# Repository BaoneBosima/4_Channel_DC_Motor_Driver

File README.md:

# Quad-Channel Motor Driver Node (STM32 & CAN)

---

## 🚀 Key Features

- **Quad-Channel Drive:** Independent control of 4 DC motors using dual high-efficiency MOSFET H-Bridges.
- **Networked Intelligence:** Onboard STM32 microcontroller offloads low-level hardware timing from the main robot computer.
- **Industrial Communication:** CAN Bus (ISO 11898) interface with impedance-controlled differential routing for high noise immunity.
- **High-Efficiency Power Stage:** Integrated synchronous buck converter delivering 95% efficiency, drastically reducing thermal waste.
- **Robust Protection:** Hardware-level reverse polarity protection (P-MOSFET) and LC noise filtering.

---

## 🛠 Hardware Specifications

| | |
| --- | --- |
| **Microcontroller** | STM32F103C8T6 (ARM Cortex-M3, 72MHz) |
| **Motor Drivers** | 2x Toshiba TB6612FNG (1.2A Continuous / 3.2A Peak per channel) |
| **Power Regulation** | MP2315 Synchronous Buck Converter (12V to 3.3V @ 3A) |
| **Transceiver** | SN65HVD230 CAN Transceiver |
| **Input Voltage** | 12V DC Nominal |
| **Max Current Rating** | 4A Continuous (Board Total) |

---

## 📐 PCB Layout & Stackup

The board was designed in KiCad 8.0 utilizing a 4-layer, impedance-controlled stackup to ensure signal integrity in a mixed-signal environment.

| Layer | Description |
| --- | --- |
| **Layer 1 (Top - Signal)** | Component placement, high-speed MCU routing, and localized thermal ground pours. |
| **Layer 2 (Inner - GND Plane)** | Solid, unbroken reference plane to minimize loop inductance, suppress EMI, and prevent ground bounce. |
| **Layer 3 (Inner - Power Plane)** | Dedicated 12V distribution plane, calculated via IPC-2221 standards to handle high-current motor transients with minimal IR drop. |
| **Layer 4 (Bottom - Signal)** | Cross-under routing, jumper traces, and bottom thermal reliefs. |

### Thermal Management

Extensive via stitching is implemented around the H-Bridge drivers and the buck converter. This couples the surface copper to the internal planes, effectively turning the PCB itself into a heatsink to handle stall currents without external cooling hardware.

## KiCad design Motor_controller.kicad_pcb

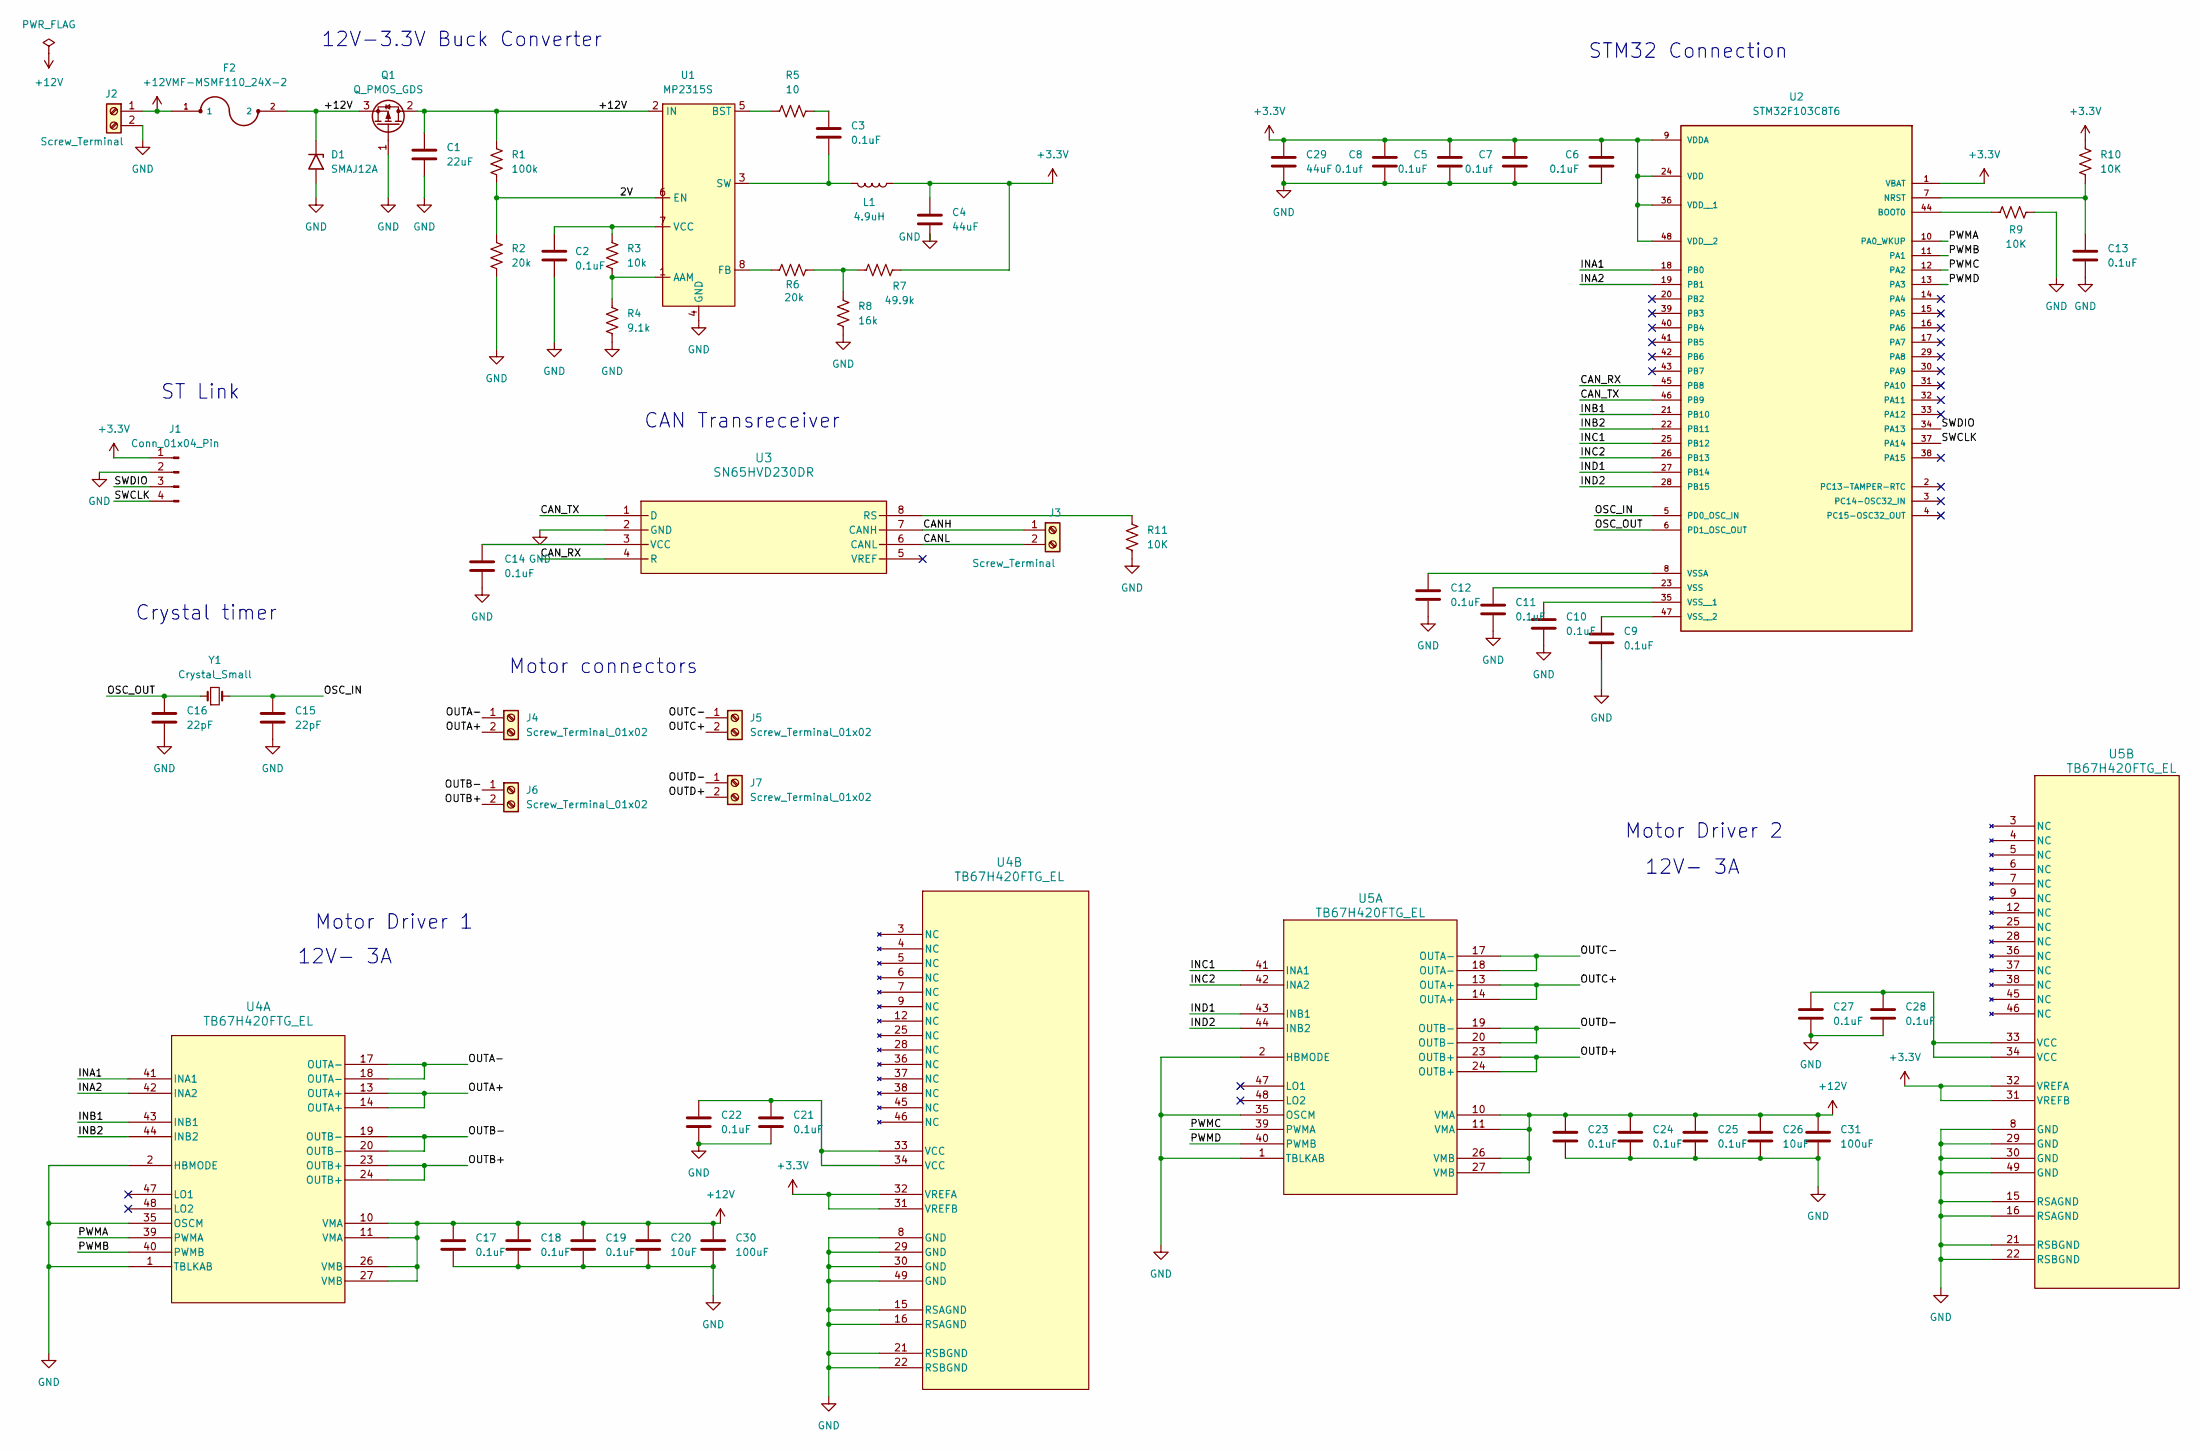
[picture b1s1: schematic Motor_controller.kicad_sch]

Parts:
C1: 22uF; C_1206_3216Metric
C2, C3, C5, C6, C9, C10, C11, C12, C13, C14, C17, C18, C19, C21, C22, C23, C24, C25, C27, C28: 0.1uF; C_0805_2012Metric
C4, C29: 44uF; CP_Elec_6.3x5.4
C7, C8: 0.1uf; C_0805_2012Metric
C15, C16: 22pF; C_0805_2012Metric
C20, C26: 10uF; C_0805_2012Metric
C30, C31: 100uF; CP_Elec_6.3x5.4
D1: SMAJ12A; D_SMA_Handsoldering
F2: MF-MSMF110_24X-2; Fuse_1812_4532Metric; DigiKey_Part_Number MF-MSMF110/24X-2CT-ND
J1: Conn_01x04_Pin; PinHeader_1x04_P2.54mm_Vertical
J2, J3: Screw_Terminal; TerminalBlock_Phoenix_MKDS-1,5-2-5.08_1x02_P5.08mm_Horizont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
J4, J5, J6, J7: Screw_Terminal_01x02; TerminalBlock_Phoenix_MKDS-1,5-2-5.08_1x02_P5.08mm_Horizont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
L1: 4.9uH; L_0805_2012Metric
Q1: Q_PMOS_GDS; TO-252-2
R1: 100k; R_0805_2012Metric
R2, R6: 20k; R_0805_2012Metric
R3: 10k; R_0805_2012Metric
R4: 9.1k; R_0805_2012Metric
R5: 10; R_0805_2012Metric
R7: 49.9k; R_0805_2012Metric
R8: 16k; R_0805_2012Metric
R9, R10, R11: 10K; R_0805_2012Metric
U1: MP2315S; TSOT-23-8
U2: STM32F103C8T6; LQFP-48-1EP_7x7mm_P0.5mm_EP3.6x3.6mm; PARTREV 10
U3: SN65HVD230DR; JEITA_SOIC-8_3.9x4.9mm_P1.27mm
U4, U5: TB67H420FTG_EL; QFN-48-1EP_7x7mm_P0.5mm_EP5.15x5.15mm_ThermalVias
Y1: Crystal_Small; Crystal_SMD_HC49-SD

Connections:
+3.3V: C4.1, C5.1, C6.1, C7.1, C8.1, C29.1, J1.1, L1.1, R7.1, R10.1, U2.1 (VBAT), U2.9 (VDDA), U2.24 (VDD), U2.36 (VDD__1), U2.48 (VDD__2), U4.31 (VREFB), U4.32 (VREFA), U5.31 (VREFB), U5.32 (VREFA)
+12V: C1.1, C17.1, C18.1, C19.1, C20.1, C23.1, C24.1, C25.1, C26.1, C30.1, C31.1, D1.1 (A1), F2.1, F2.2, J2.1, Q1.2 (D), Q1.3 (S), R1.1, U1.2 (IN), U4.10 (VMA), U4.11 (VMA), U4.26 (VMB), U4.27 (VMB), U5.10 (VMA), U5.11 (VMA), U5.26 (VMB), U5.27 (VMB)
/2V: R1.2, R2.1, U1.6 (EN)
/CANH: J3.1, U3.7 (CANH)
/CANL: J3.2, U3.6 (CANL)
/CAN_RX: U2.45 (PB8), U3.4 (R)
/CAN_TX: U2.46 (PB9), U3.1 (D)
/INA1: U2.18 (PB0), U4.41 (INA1)
/INA2: U2.19 (PB1), U4.42 (INA2)
/INB1: U2.21 (PB10), U4.43 (INB1)
/INB2: U2.22 (PB11), U4.44 (INB2)
/INC1: U2.25 (PB12), U5.41 (INA1)
/INC2: U2.26 (PB13), U5.42 (INA2)
/IND1: U2.27 (PB14), U5.43 (INB1)
/IND2: U2.28 (PB15), U5.44 (INB2)
/OSC_IN: C15.1, U2.5 (PD0_OSC_IN), Y1.2
/OSC_OUT: C16.1, U2.6 (PD1_OSC_OUT), Y1.1
/OUTA+: J4.2, U4.13 (OUTA+), U4.14 (OUTA+)
/OUTA-: J4.1, U4.17 (OUTA-), U4.18 (OUTA-)
/OUTB+: J6.2, U4.23 (OUTB+), U4.24 (OUTB+)
/OUTB-: J6.1, U4.19 (OUTB-), U4.20 (OUTB-)
/OUTC+: J5.2, U5.13 (OUTA+), U5.14 (OUTA+)
/OUTC-: J5.1, U5.17 (OUTA-), U5.18 (OUTA-)
/OUTD+: J7.2, U5.23 (OUTB+), U5.24 (OUTB+)
/OUTD-: J7.1, U5.19 (OUTB-), U5.20 (OUTB-)
/PWMA: U2.10 (PA0_WKUP), U4.39 (PWMA)
/PWMB: U2.11 (PA1), U4.40 (PWMB)
/PWMC: U2.12 (PA2), U5.39 (PWMA)
/PWMD: U2.13 (PA3), U5.40 (PWMB)
/SWCLK: J1.4, U2.37 (PA14)
/SWDIO: J1.3, U2.34 (PA13)
GND: C1.2, C2.2, C4.2, C5.2, C6.2, C7.2, C8.2, C9.2, C10.2, C11.2, C12.2, C13.2, C14.2, C15.2, C16.2, C17.2, C18.2, C19.2, C20.2, C21.2, C22.2, C23.2, C24.2, C25.2, C26.2, C27.2, C28.2, C29.2, C30.2, C31.2, D1.2 (A2), J1.2, J2.2, Q1.1 (G), R2.2, R4.2, R8.2, R9.1, R11.2, U1.4 (GND), U3.2 (GND), U4.1 (TBLKAB), U4.2 (HBMODE), U4.8 (GND), U4.15 (RSAGND), U4.16 (RSAGND), U4.21 (RSBGND), U4.22 (RSBGND), U4.29 (GND), U4.30 (GND), U4.35 (OSCM), U4.49 (GND), U5.1 (TBLKAB), U5.2 (HBMODE), U5.8 (GND), U5.15 (RSAGND), U5.16 (RSAGND), U5.21 (RSBGND), U5.22 (RSBGND), U5.29 (GND), U5.30 (GND), U5.35 (OSCM), U5.49 (GND)
unnamed: C3.1, R5.1
unnamed: C21.1, C22.1, U4.33 (VCC), U4.34 (VCC)
unnamed: C27.1, C28.1, U5.33 (VCC), U5.34 (VCC)
unnamed: R6.1, R7.2, R8.1
unnamed: R3.2, R4.1, U1.1 (AAM)
unnamed: R5.2, U1.5 (BST)
unnamed: R6.2, U1.8 (FB)
unnamed: C3.2, L1.2, U1.3 (SW)
unnamed: C2.1, R3.1, U1.7 (VCC)
unnamed: R9.2, U2.44 (BOOT0)
unnamed: C13.1, R10.2, U2.7 (NRST)
unnamed: C11.1, U2.23 (VSS)
unnamed: C12.1, U2.8 (VSSA)
unnamed: C10.1, U2.35 (VSS__1)
unnamed: C9.1, U2.47 (VSS__2)
unnamed: R11.1, U3.8 (RS)
unnamed: C14.1, U3.3 (VCC)

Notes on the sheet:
Motor Driver 1
12V- 3A
Crystal timer
Motor connectors
Motor Driver 2
ST Link
12V-3.3V Buck Converter
CAN Transreceiver
STM32 Connection

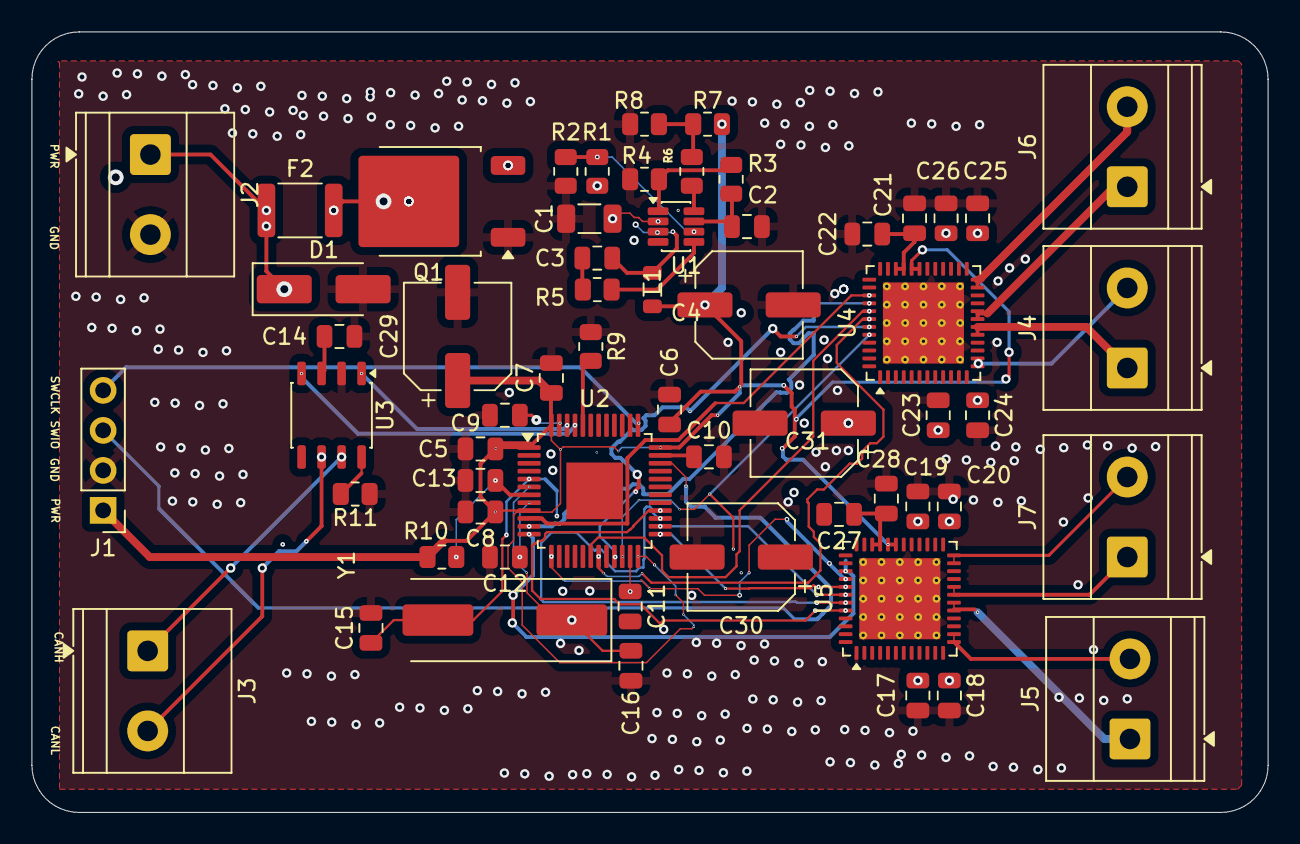
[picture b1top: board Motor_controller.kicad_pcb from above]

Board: 4 copper layers, 78.5 x 49.5 mm, 59 parts (0 on the bottom side), 49 nets.

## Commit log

2026-03-30 Initial commit: KiCad 4-channel DC motor driver project
    Made-with: Cursor
2026-03-30 cleanup
2026-03-30 Add README
    Added detailed information about the Quad-Channel Motor Driver, including key features, hardware specifications, PCB layout, and thermal management.
2026-03-30 Added pictures of PCB
